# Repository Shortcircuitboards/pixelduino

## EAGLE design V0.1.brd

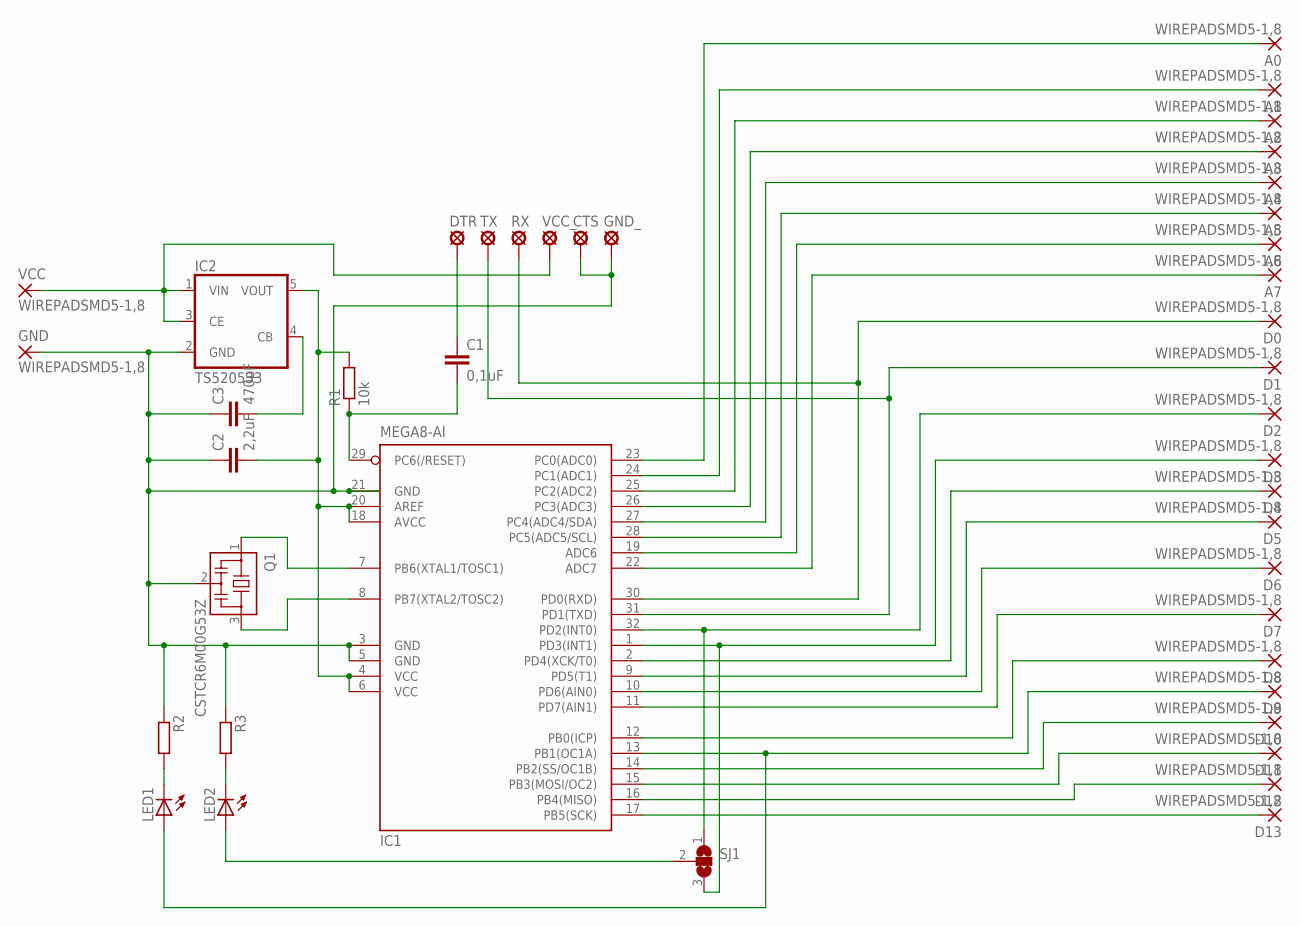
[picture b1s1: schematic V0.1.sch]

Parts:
A0, A1, A2, A3, A4, A5, A6, A7: WIREPADSMD5-1,8; 5-1,8
C1: 0,1uF; C0603
C2: 2,2uF; C0603
C3: 470pF; C0603
CTS: LSP10
D0, D1, D2, D3, D4, D5, D6, D7, D8, D9, D10, D11, D12, D13: WIREPADSMD5-1,8; 5-1,8
DTR: LSP10
GND: WIREPADSMD5-1,8; 5-1,8
GND_: LSP10
IC1: MEGA8-AI; TQFP32-08; MPN ATMEGA328P-16AU
IC2: TS520533; SOT25
LED1, LED2: LEDCHIP-LED0603; CHIP-LED0603
Q1: CSTCR6M00G53Z; CSTCR6M
R1: 10k; R0603
R2, R3: R-EU_R0603; R0603
RX: LSP10
SJ1: SJ2W; SJ_2
TX: LSP10
VCC: WIREPADSMD5-1,8; 5-1,8
VCC_: LSP10

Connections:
unnamed: IC1.8 (PB7(XTAL2/TOSC2)), Q1.3
unnamed: IC1.7 (PB6(XTAL1/TOSC1)), Q1.1
unnamed: C2.1, C3.1, CTS.MP, GND.1, GND_.MP, IC1.3 (GND), IC1.5 (GND), IC1.21 (GND), IC2.2 (GND), Q1.2, R2.1, R3.1
unnamed: IC2.1 (VIN), IC2.3 (CE), VCC.1, VCC_.MP
unnamed: C2.2, IC1.4 (VCC), IC1.6 (VCC), IC1.18 (AVCC), IC1.20 (AREF), IC2.5 (VOUT), R1.2
unnamed: D2.1, IC1.32 (PD2(INT0)), SJ1.1
unnamed: D1.1, IC1.31 (PD1(TXD)), TX.MP
unnamed: D0.1, IC1.30 (PD0(RXD)), RX.MP
unnamed: D3.1, IC1.1 (PD3(INT1)), SJ1.3
unnamed: D4.1, IC1.2 (PD4(XCK/T0))
unnamed: D5.1, IC1.9 (PD5(T1))
unnamed: D6.1, IC1.10 (PD6(AIN0))
unnamed: D7.1, IC1.11 (PD7(AIN1))
unnamed: D8.1, IC1.12 (PB0(ICP))
unnamed: D9.1, IC1.13 (PB1(OC1A)), LED1.A
unnamed: D10.1, IC1.14 (PB2(SS/OC1B))
unnamed: D11.1, IC1.15 (PB3(MOSI/OC2))
unnamed: D12.1, IC1.16 (PB4(MISO))
unnamed: D13.1, IC1.17 (PB5(SCK))
unnamed: A0.1, IC1.23 (PC0(ADC0))
unnamed: A1.1, IC1.24 (PC1(ADC1))
unnamed: A2.1, IC1.25 (PC2(ADC2))
unnamed: A3.1, IC1.26 (PC3(ADC3))
unnamed: A4.1, IC1.27 (PC4(ADC4/SDA))
unnamed: A5.1, IC1.28 (PC5(ADC5/SCL))
unnamed: A6.1, IC1.19 (ADC6)
unnamed: A7.1, IC1.22 (ADC7)
unnamed: LED1.C, R2.2
unnamed: LED2.C, R3.2
unnamed: C1.2, IC1.29 (PC6(/RESET)), R1.1
unnamed: C1.1, DTR.MP
unnamed: LED2.A, SJ1.2
unnamed: C3.2, IC2.4 (CB)

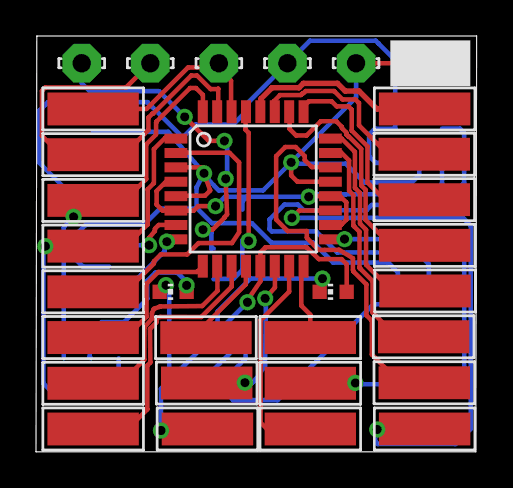
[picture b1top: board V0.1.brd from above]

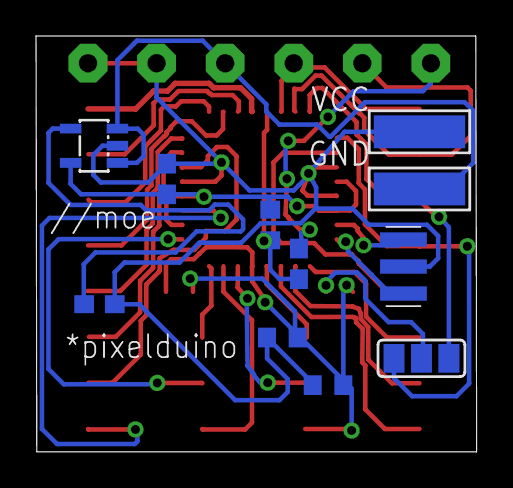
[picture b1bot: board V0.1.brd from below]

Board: 2 copper layers, 24.5 x 23.1 mm, 44 parts (13 on the bottom side), 33 nets.

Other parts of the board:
U$1: //MOE
U$2: ARDUINO

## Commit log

2015-11-13 :neckbeard: Added .gitattributes & .gitignore files
2015-11-13 Egale Files Up
    I uploaded the Eagle files of the V0.1
